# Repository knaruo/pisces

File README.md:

# pisces
Pisces - Tiny Split Keyboard

# Concept

* Ortholinear
  * 3 rows \* 6 columns + 1 thumb key, total 38 keys
* Key switch hot-swap capable
  * Supports Kailh PCB socket for MX
* Thin design
  * Only supports SMT diodes (1N4148W)

# BOM list

Number of components in the following bill of material table is for one hand.

**Here are the mandatory items:**
| Name         | Parts id       | Number | Note                                                                                    |
| ------------ | -------------- | ------ | --------------------------------------------------------------------------------------- |
| Diode        | 1N4148W        | 19     | Availaable from [here](https://akizukidenshi.com/catalog/g/gI-07084/)                   |
| ATmega32U2     | -              | 1      | |
| TRRS jack    | PRT-12639      | 1      | Available from [here](https://www.sengoku.co.jp/mod/sgk_cart/detail.php?code=EEHD-4VML) |
| TRRS cable   | -              | 1      |                                                                                         |
| Reset Switch | TVAF06-A020B-R | 1      | Available from [here](https://akizukidenshi.com/catalog/g/gP-14888/)                    |

**For Cherry MX profile:**

| Name             | Parts id     | Number | Note                                                                                                    |
| ---------------- | ------------ | ------ | ------------------------------------------------------------------------------------------------------- |
| Socket (MX)      | CPG151101S11 | 19     | [here](https://kbdfans.com/collections/switches/products/mechanical-keyboard-switches-kailh-pcb-socket) |
| Spacer (M2 7mm)  | ARB-2007E    | 6      | [here](https://www.hirosugi-net.co.jp/shop/g/g2392/)                                                    |
| Thread (M2 3mm)  | -            | 12     | [here for example..](https://www.amazon.co.jp/dp/B083DR1YQL/ref=cm_sw_em_r_mt_dp_sWb6FbA93WCSS)         |

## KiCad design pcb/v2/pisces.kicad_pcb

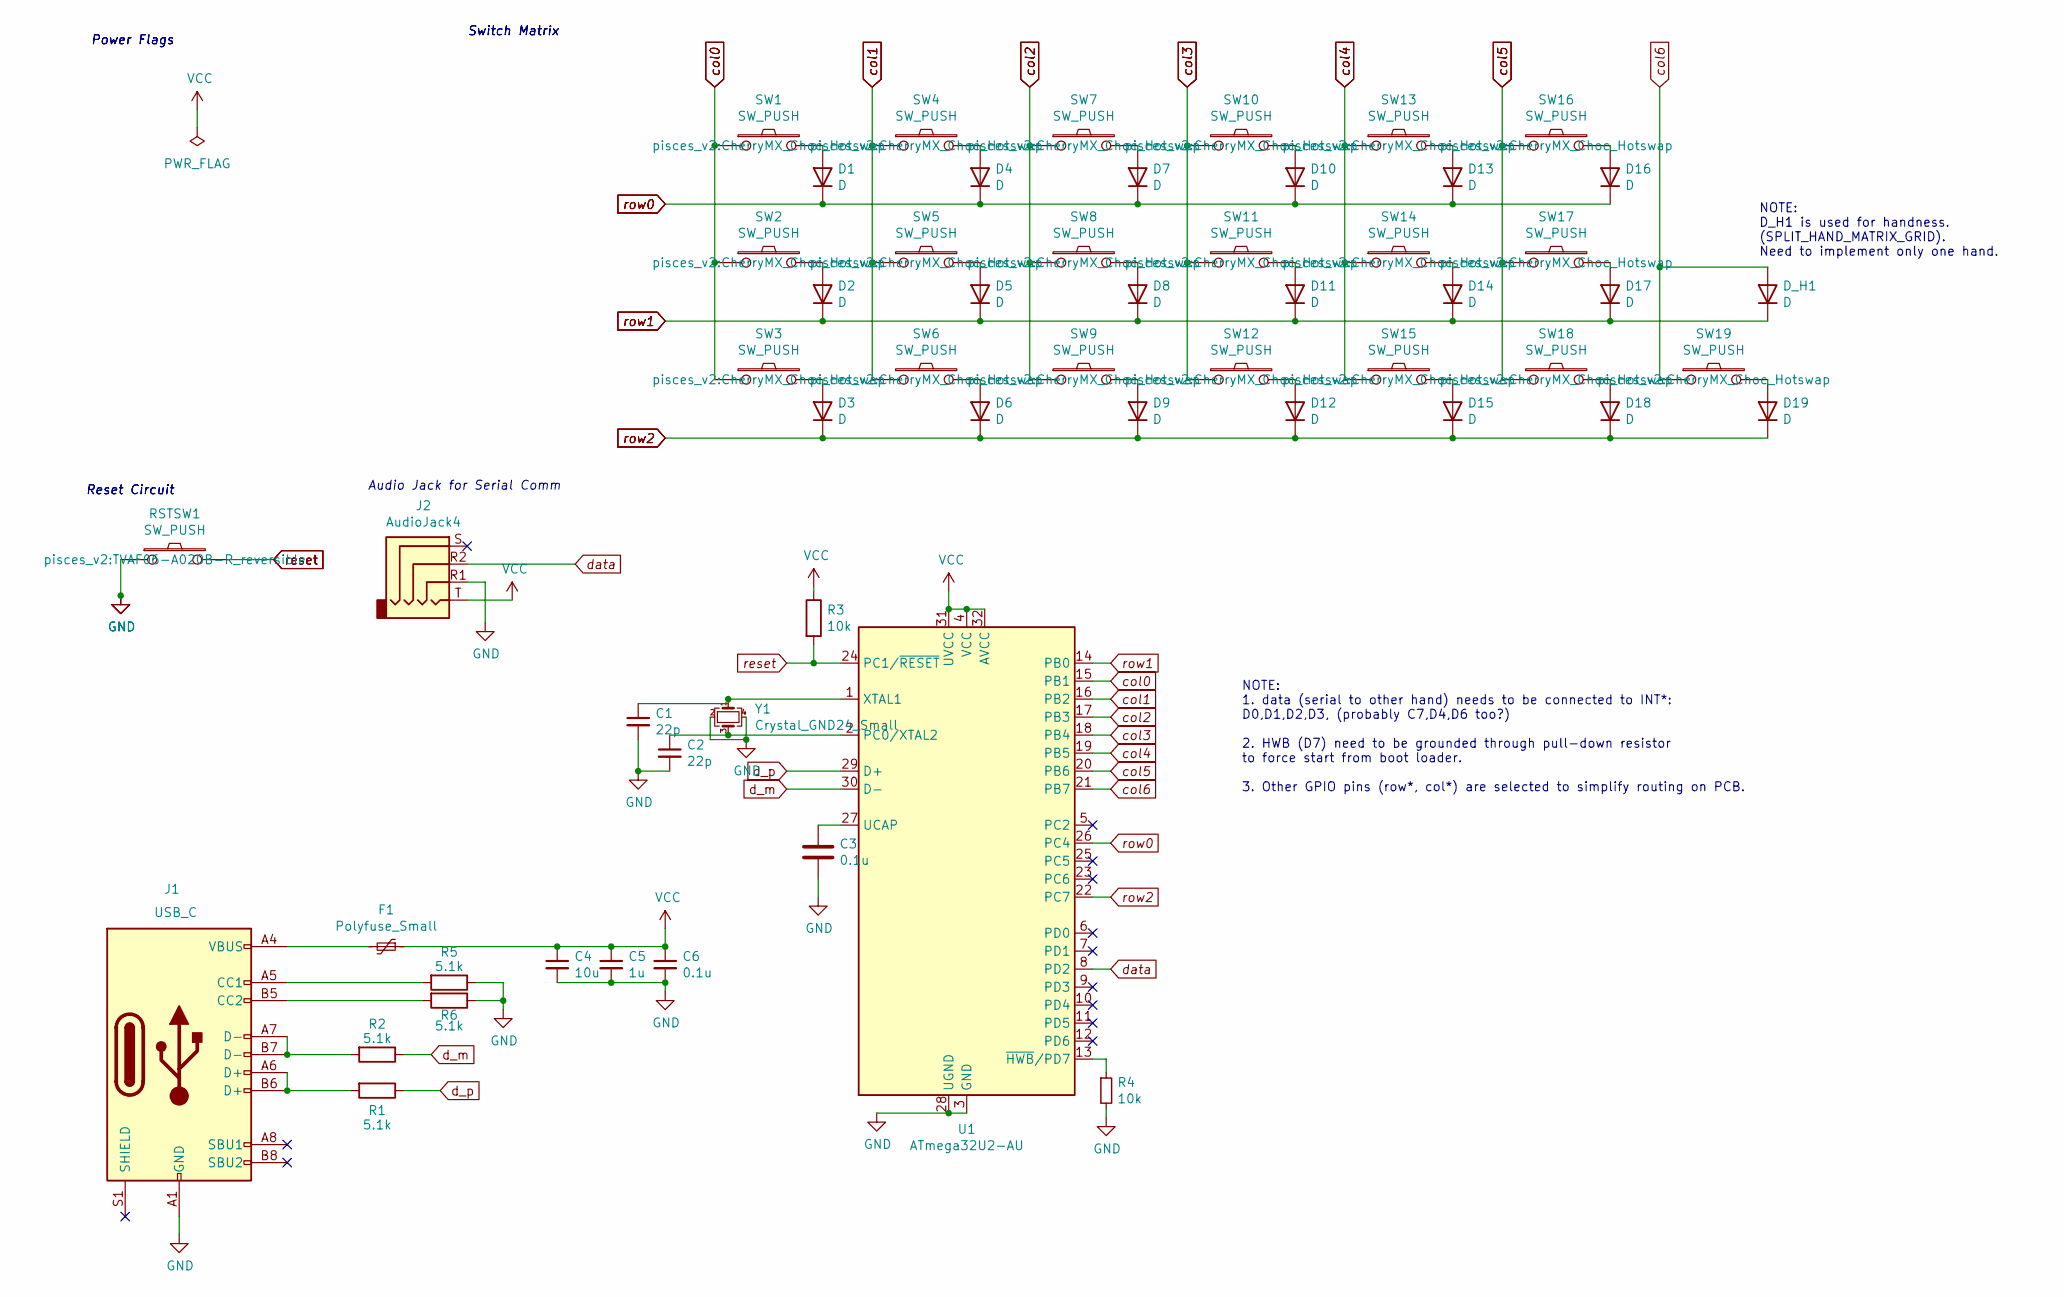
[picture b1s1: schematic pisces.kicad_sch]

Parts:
C1, C2: 22p; C_0402_1005Metric
C3, C6: 0.1u; C_0402_1005Metric
C4: 10u; C_0805_2012Metric
C5: 1u; C_0603_1608Metric
D1, D2, D3, D4, D5, D6, D7, D8, D9, D10, D11, D12, D13, D14, D15, D16, D17, D18, D19: D; D3_SMD
D_H1: D; D3_SMD
F1: Polyfuse_Small; RESC1206X70N
J1: USB_C; USB_C_Receptacle_XKB_U262-16XN-4BVC11
J2: AudioJack4; Jack_3.5mm_PJ320D_Horizontal_reversible
R1, R2: 5.1k; R_0603_1608Metric
R3, R4: 10k; R_0603_1608Metric
R5, R6: 5.1k; R_0402_1005Metric
RSTSW1: SW_PUSH; TVAF06-A020B-R_reversible
SW1, SW2, SW3, SW4, SW5, SW6, SW7, SW8, SW9, SW10, SW11, SW12, SW13, SW14, SW15, SW16, SW17, SW18, SW19: SW_PUSH; CherryMX_Choc_Hotswap
U1: ATmega32U2-AU; TQFP-32_7x7mm_P0.8mm
Y1: Crystal_GND24_Small; Crystal_SMD_SeikoEpson_FA238-4Pin_3.2x2.5mm

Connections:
GND: C1.2, C2.2, C3.2, C4.2, C5.2, C6.2, J1.A1 (GND), J1.A12 (GND), J1.B1 (GND), J1.B12 (GND), J2.R1, R4.2, R5.1, R6.1, RSTSW1.1, U1.3 (GND), U1.28 (UGND), Y1.2, Y1.4
unnamed: D1.2 (A), SW1.2
unnamed: D2.2 (A), SW2.2
unnamed: D3.2 (A), SW3.2
unnamed: D4.2 (A), SW4.2
unnamed: D5.2 (A), SW5.2
unnamed: D6.2 (A), SW6.2
unnamed: D7.2 (A), SW7.2
unnamed: D8.2 (A), SW8.2
unnamed: D9.2 (A), SW9.2
unnamed: D10.2 (A), SW10.2
unnamed: D11.2 (A), SW11.2
unnamed: D12.2 (A), SW12.2
unnamed: D13.2 (A), SW13.2
unnamed: D14.2 (A), SW14.2
unnamed: D15.2 (A), SW15.2
unnamed: D16.2 (A), SW16.2
unnamed: D17.2 (A), SW17.2
unnamed: D18.2 (A), SW18.2
unnamed: D19.2 (A), SW19.2
unnamed: F1.2, J1.A4 (VBUS), J1.A9 (VBUS), J1.B4 (VBUS), J1.B9 (VBUS)
unnamed: J1.A5 (CC1), R5.2
unnamed: J1.B5 (CC2), R6.2
unnamed: J1.A6 (D+), J1.B6 (D+), R1.2
unnamed: J1.A7 (D-), J1.B7 (D-), R2.2
unnamed: C2.1, U1.2 (PC0/XTAL2), Y1.3
unnamed: C3.1, U1.27 (UCAP)
unnamed: C1.1, U1.1 (XTAL1), Y1.1
unnamed: R4.1, U1.13 (~HWB/PD7)
VCC: C4.1, C5.1, C6.1, F1.1, J2.T, R3.1, U1.4 (VCC), U1.31 (UVCC), U1.32 (AVCC)
col0: SW1.1, SW2.1, SW3.1, U1.15 (PB1)
col1: SW4.1, SW5.1, SW6.1, U1.16 (PB2)
col2: SW7.1, SW8.1, SW9.1, U1.17 (PB3)
col3: SW10.1, SW11.1, SW12.1, U1.18 (PB4)
col4: SW13.1, SW14.1, SW15.1, U1.19 (PB5)
col5: SW16.1, SW17.1, SW18.1, U1.20 (PB6)
col6: D_H1.2 (A), SW19.1, U1.21 (PB7)
d_m: R2.1, U1.30 (D-)
d_p: R1.1, U1.29 (D+)
data: J2.R2, U1.8 (PD2)
reset: R3.2, RSTSW1.2, U1.24 (PC1/~RESET)
row0: D1.1 (K), D4.1 (K), D7.1 (K), D10.1 (K), D13.1 (K), D16.1 (K), U1.26 (PC4)
row1: D2.1 (K), D5.1 (K), D8.1 (K), D11.1 (K), D14.1 (K), D17.1 (K), D_H1.1 (K), U1.14 (PB0)
row2: D3.1 (K), D6.1 (K), D9.1 (K), D12.1 (K), D15.1 (K), D18.1 (K), D19.1 (K), U1.22 (PC7)

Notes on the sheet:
Audio Jack for Serial Comm
Power Flags
Switch Matrix
Reset Circuit
NOTE: D_H1 is used for handness. (SPLIT_HAND_MATRIX_GRID). Need to implement only one hand.
NOTE: 1. data (serial to other hand) needs to be connected to INT*: D0,D1,D2,D3, (probably C7,D4,D6 too?) 2. HWB (D7) need to be grounded through pull-down resistor to force start from boot loader. 3. Other GPIO pins (row*, col*) are selected to simplify routing on PCB.

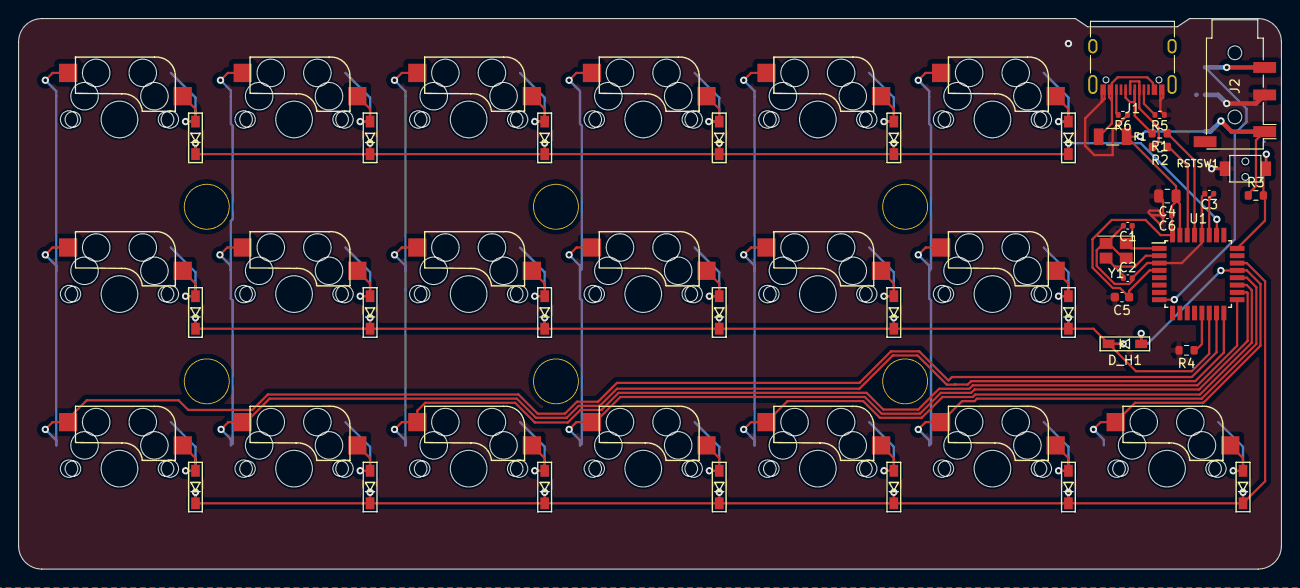
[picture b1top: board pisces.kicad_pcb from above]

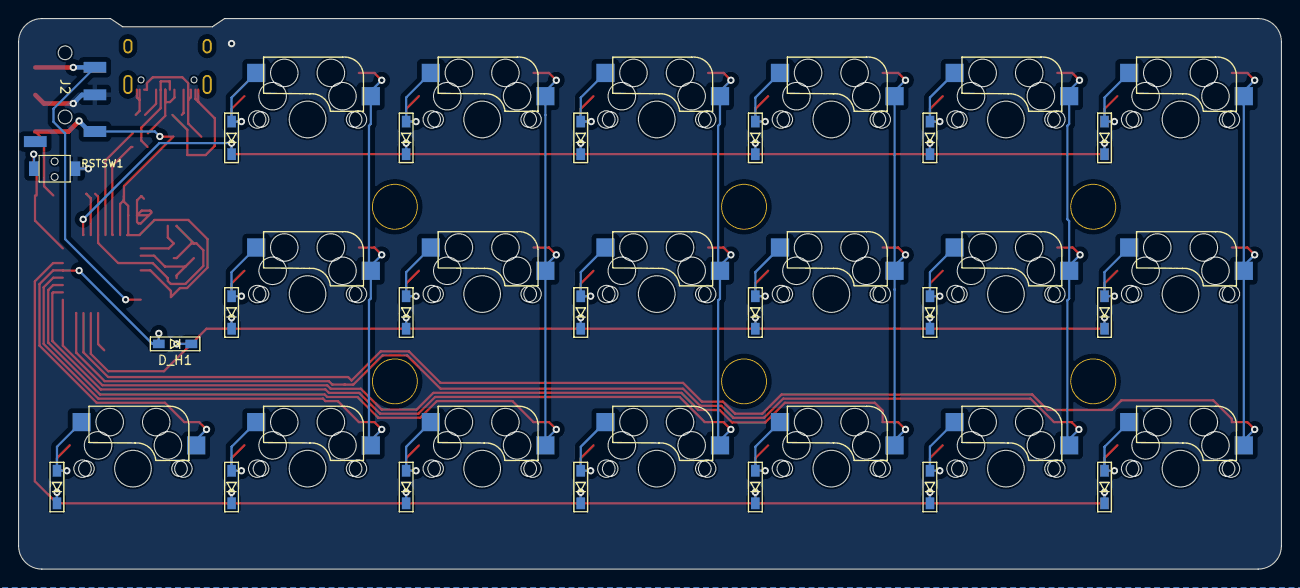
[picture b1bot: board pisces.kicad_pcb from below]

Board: 2 copper layers, 137.8 x 60.1 mm, 63 parts (19 on the bottom side), 44 nets.

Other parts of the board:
HOLE1, HOLE2, HOLE7, HOLE8, HOLE13, HOLE14: Val**; HOLE

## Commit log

2020-11-21 Copied barracuda
2020-11-21 Generated .net and .kicad_pcb
2020-11-21 Fixed the switches, diodes, and mounting holes' position
2020-11-21 Connected row/col/switches tracks
2020-11-21 Rough Edge.Cut drawing
2020-11-22 Connected all tracks other than GND
2020-12-04 almost done with the layout
2020-12-04 Issue1 copy barracuda (#2)
    * Copied barracuda
    * Generated .net and .kicad_pcb
    * Fixed the switches, diodes, and mounting holes' position
    * Connected row/col/switches tracks
    * Rough Edge.Cut drawing
    * Connected all tracks other than GND
2020-12-04 Added a audio jack and connected tracks
2020-12-04 Filled GND area
2020-12-04 Aligned mounting holes
2020-12-04 Issue3 add jack (#4)
    * Added a audio jack and connected tracks
    * Filled GND area
    * Aligned mounting holes
2020-12-04 Updated foot prints to reversible
2020-12-04 Updated foot prints to reversible (#6)
2020-12-05 Added pisces bottom plate
2020-12-05 Added pisces bottom plate (#8)
2020-12-05 Added top plate
2020-12-06 Added top plate (#10)
2020-12-06 Added support plate design
2020-12-06 Added support plate design (#12)
2020-12-07 Added generated gerber files for ordering to JLCPCB
2020-12-07 Added generated gerber files for ordering to JLCPCB (#15)
2020-12-27 Added how it looks
2020-12-27 Added overview
2020-12-27 Added BOM list
2020-12-27 Issue17 readme (#18)
    * Added how it looks
    * Added overview
    * Added BOM list
2021-01-10 draft
2021-01-10 Done with routing
2021-01-24 PCB almost there...
2021-01-24 Added signiture on PCB
2021-01-24 bottom plate is done
2021-01-24 done with top plate
2021-02-28 Pisces V2 ordered PCB with these gerber files
2021-02-28 Issue19 v2 design (#20)
    * draft
    * Done with routing
    * PCB almost there...
    * Added signiture on PCB
    * bottom plate is done
    * done with top plate
2021-02-28 pisces V2.1 option 2 (SPLIT_HAND_MATRIX_GRID)
2021-03-01 Regenerated pisces pcb gerber files
2021-03-17 Pcb 2.1 op2 (#22)
    * pisces V2.1 option 2 (SPLIT_HAND_MATRIX_GRID)
    * Regenerated pisces pcb gerber files
2021-03-17 Very quick fix on the README.md to bring PCB2.1 as mainline.
2021-03-17 Very quick fix on the README.md to bring PCB2.1 as mainline. (#24)
2021-07-24 bottom plate: Acrylic
2021-07-24 Added template for Emerge+
2021-07-24 Bottom plate: DONE
2021-07-24 Top plate is DONE as well
2021-07-25 draft of mid spacer
2021-07-25 draft mid spacer
2021-07-25 Mid spacer draft
2021-07-25 Added cropped area around MCU
2021-07-26 Removed fill
2024-12-28 Updated KiCad version to 8.0, Supported JLCPCB PCBA info
2024-12-28 Updated KiCad version to 8.0, Supported JLCPCB PCBA info (#27)
2024-12-28 Verified that the current drawing is okay on KiCad 5.1.12
2024-12-28 Revert "Updated KiCad version to 8.0, Supported JLCPCB PCBA info (#27)"
    This reverts commit 94e640e821e110d7bb05b34c9f22027f3d2cd6e9.
2024-12-28 Revert "Updated KiCad version to 8.0, Supported JLCPCB PCBA info (#27)" (#28)
    This reverts commit 94e640e821e110d7bb05b34c9f22027f3d2cd6e9.
2024-12-28 Verified that the current drawing is okay on KiCad 5.1.12 (#29)
2024-12-28 Removed R5 (resistor) from schematic
2024-12-28 Removed R5 (resistor) from schematic (#30)
2024-12-28 Stopped using hand-soldering footprint for most of parts
2024-12-28 Stopped using hand-soldering footprint for most of parts (#31)
2024-12-28 Resistors: 0805 --> 0603, Capacitors (other than 10u): 0603
2024-12-28 Smaller parts footprint
2024-12-28 Used smaller parts footprint (Resistors and Capacitors) (#32)
    * Resistors: 0805 --> 0603, Capacitors (other than 10u): 0603
    * Smaller parts footprint
2024-12-28 Removed external link to footprint library
2024-12-28 Removed external link to footprint library (#33)
2024-12-28 KiCad Updated to 6.0.7
2024-12-28 KiCad Updated to 6.0.7 (#34)
2024-12-29 Removed ERC errors as many as possible
2024-12-29 symbols も外部依存をなくした
2024-12-29 Updated KiCad 7.0.10 (#35)
    * Removed ERC errors as many as possible
    * symbols も外部依存をなくした
2024-12-29 KiCad updated to 8.0.7
2024-12-29 KiCad updated to 8.0.7 (#36)
2024-12-29 JLCPCB support
2024-12-29 JLCPCB support (#37)
2024-12-29 USB-C foot printをコピーしてきた
2024-12-30 USB-C version
2024-12-30 version should be 2.2
2024-12-30 Update pisces.kicad_pro
    more exclusion
2024-12-30 Updated USB connector from Micro-B to USB-C (pisces ver 2.2) (#38)
    * USB-C foot printをコピーしてきた
    * USB-C version
    * version should be 2.2
    * Update pisces.kicad_pro
    more exclusion
